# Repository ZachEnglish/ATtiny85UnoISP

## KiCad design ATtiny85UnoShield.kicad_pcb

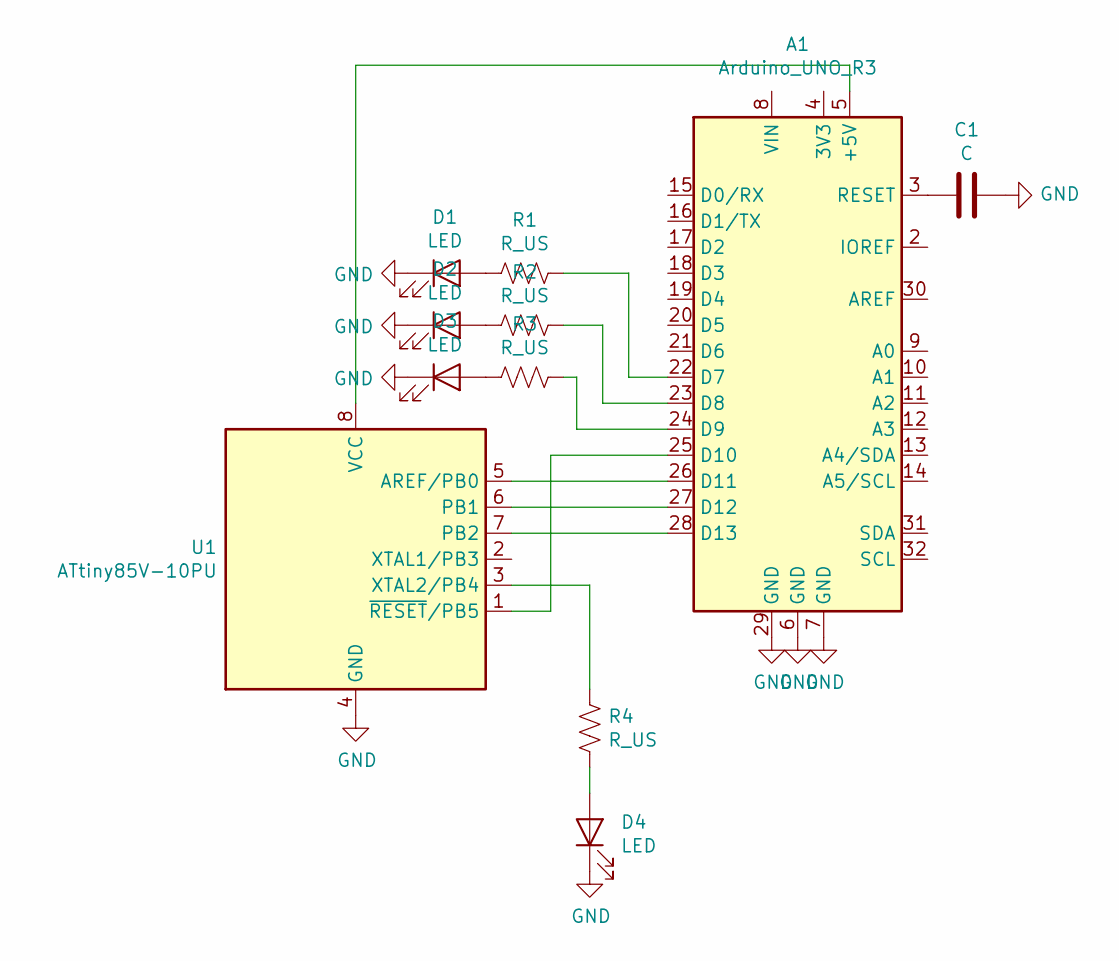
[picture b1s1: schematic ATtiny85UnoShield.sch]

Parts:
A1: Arduino_UNO_R3
C1: C; CP_Radial_D6.3mm_P2.50mm
D1, D2, D3, D4: LED; LED_D5.0mm
R1, R2, R3, R4: R_US; R_Axial_DIN0207_L6.3mm_D2.5mm_P10.16mm_Horizontal
U1: ATtiny85V-10PU; DIP-8_W7.62mm

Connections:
GND: A1.6 (GND), A1.7 (GND), A1.29 (GND), C1.2, D1.1 (K), D2.1 (K), D3.1 (K), D4.1 (K), U1.4 (GND)
unnamed: A1.3 (RESET), C1.1
unnamed: A1.5 (+5V), U1.8 (VCC)
unnamed: A1.22 (D7), R1.1
unnamed: A1.23 (D8), R2.1
unnamed: A1.24 (D9), R3.1
unnamed: A1.25 (D10), U1.1 (~RESET~/PB5)
unnamed: A1.26 (D11), U1.5 (AREF/PB0)
unnamed: A1.27 (D12), U1.6 (PB1)
unnamed: A1.28 (D13), U1.7 (PB2)
unnamed: D1.2 (A), R1.2
unnamed: D2.2 (A), R2.2
unnamed: D3.2 (A), R3.2
unnamed: D4.2 (A), R4.2
unnamed: R4.1, U1.3 (XTAL2/PB4)

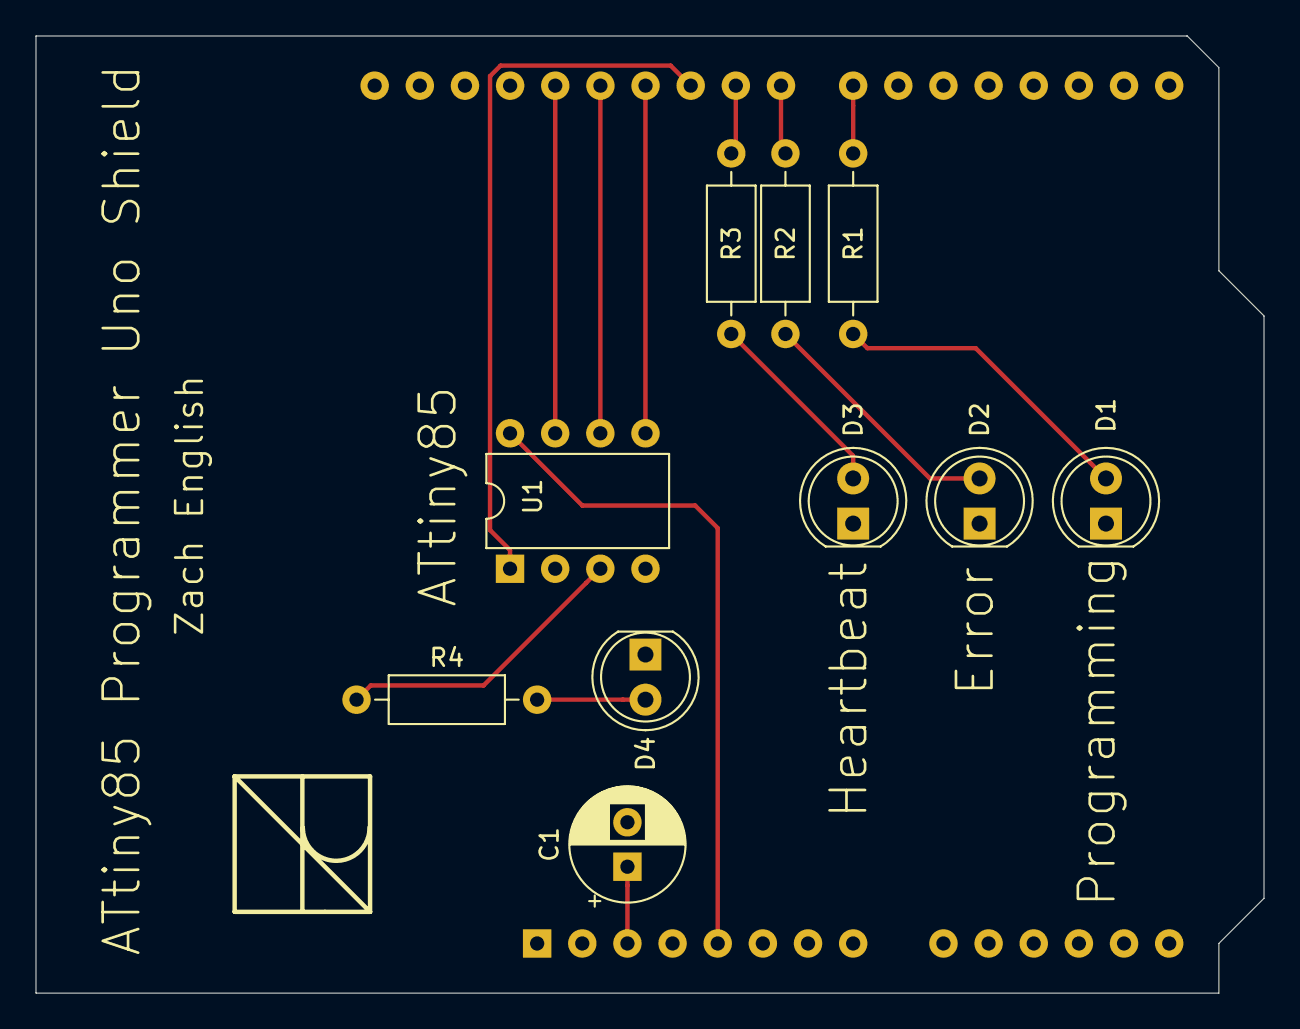
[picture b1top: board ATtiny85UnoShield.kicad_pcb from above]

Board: 2 copper layers, 69.1 x 53.8 mm, 11 parts (1 on the bottom side), 15 nets.

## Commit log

2021-01-22 Initial commit, project was fast and quick.
    Already ordered PCBs....
2021-01-22 Added missing footprint library file to repo
2021-03-08 Added PDF instructions on how to set up the Arduino IDE to program the ATtiny85 using this shield.
